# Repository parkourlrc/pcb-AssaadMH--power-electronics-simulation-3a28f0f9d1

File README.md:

# Power Electronics Design & Simulation Suite
> AC power controllers, a 0–10 V industrial dimmer, a digital tachometer and a brushless drive, designed and simulated end to end.
`2025` · `Proteus` · `Power electronics` · `Analog design` · `Microcontroller` · `PSIM`

## About

A body of power-electronics design work carried through schematic capture and full mixed-signal simulation before any board was built.

It covers phase-angle AC power controllers (including a capacitive-trigger variant), a 0–10 V industrial power regulator matching the standard control-signal interface used on drives and dimmable ballasts, a microcontroller-based digital tachometer, and a brushless motor drive — alongside characterisation work on transistor stages and power amplifiers.

Simulating first is the point: switching topologies punish the difference between a circuit that works on paper and one that survives a real inductive load.

## Contents

```
captures/
docs/
kicad/
```

## Notes

## Documents

- [`docs/gradateur-0-10V-projet-tutore.pptx`](docs/gradateur-0-10V-projet-tutore.pptx): the tutored-project defence for the **0-10 V power dimmer** (ENIG, 2024/2025), by Mahmoudi Lassaad, Omri Salim and Dhaoui Chahin. It covers the 7812 supply, the LM358 stage, the PWM power control, the simulation and the PCB. The related boards are `kicad/VARIATEUR_0_10V/` and `kicad/GRADATEUR_DE_PUISSANCE/`.

## Third-party work used here

Everything in this repository is my own work. It builds on the following, which are **not** mine and are used under their own licences:

- **KiCad** by KiCad project — <https://kicad.org>
- **Proteus Design Suite** by Labcenter Electronics — <https://labcenter.com>

## Author

Lassaad Mahmoudi — <assaadmahmoudi0@gmail.com>  
https://linkedin.com/in/mahmoudi-assaad

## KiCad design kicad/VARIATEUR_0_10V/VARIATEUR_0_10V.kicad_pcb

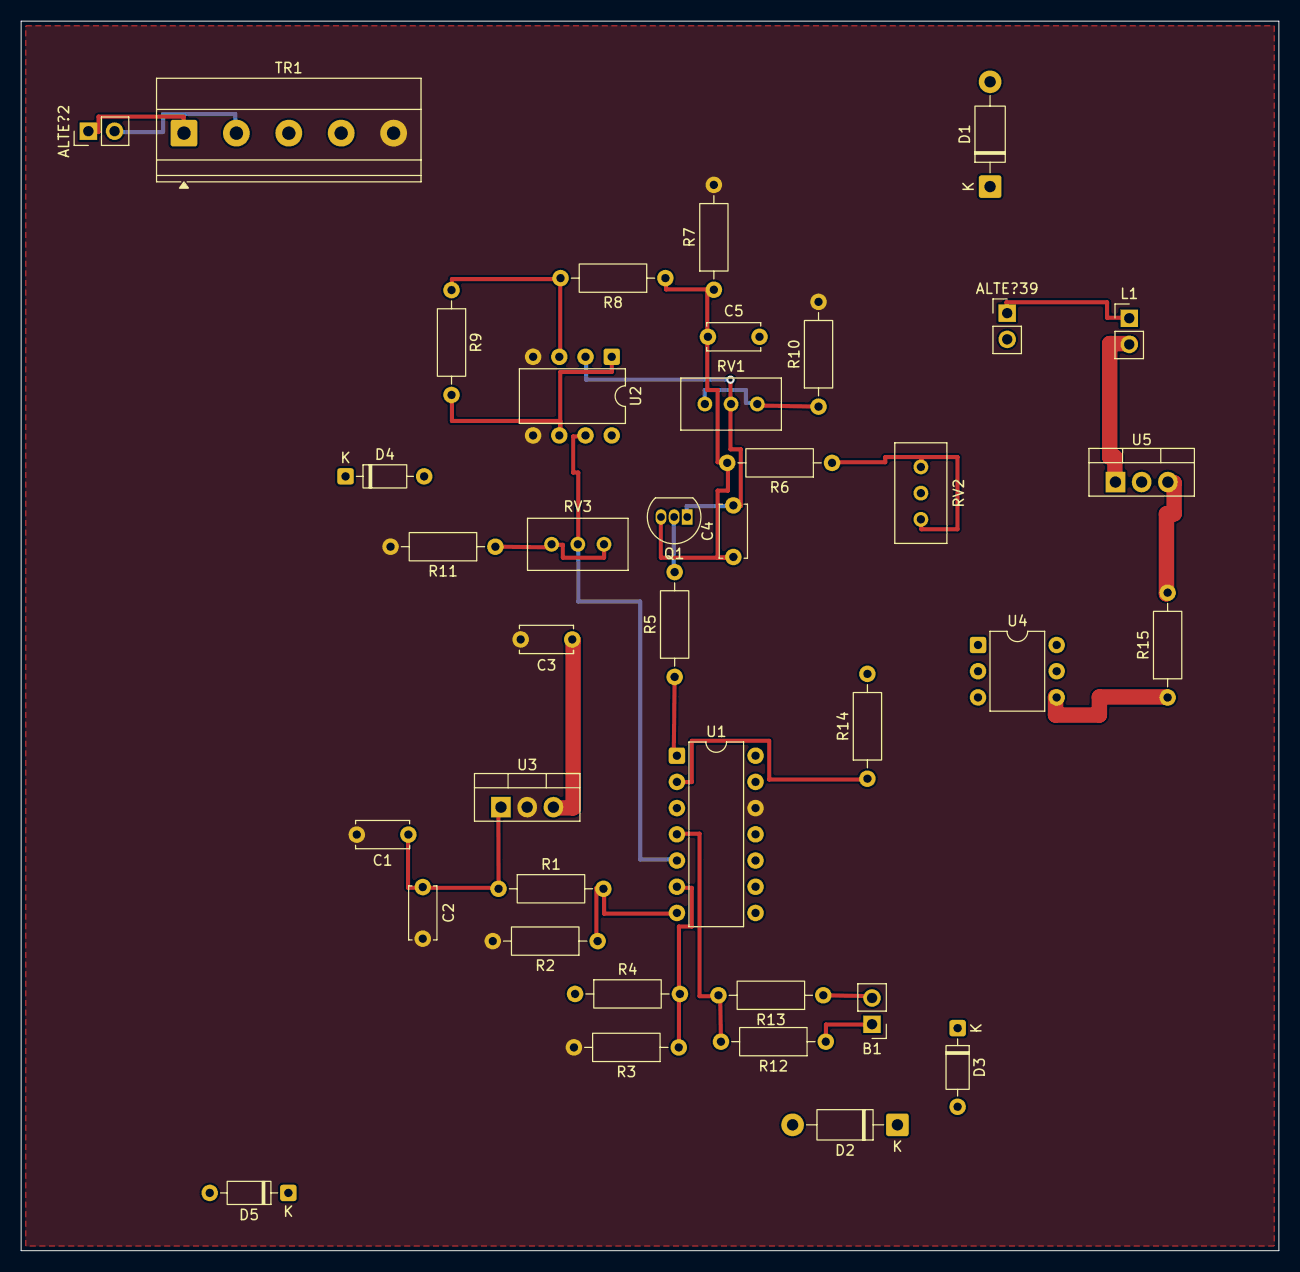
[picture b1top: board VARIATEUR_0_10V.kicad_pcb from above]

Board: 2 copper layers, 121.9 x 119.2 mm, 39 parts (0 on the bottom side), 27 nets.

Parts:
ALTE?2, ALTE?39: ALTERNATOR; PinHeader_1x02_P2.54mm_Vertical
B1: 0V; PinHeader_1x02_P2.54mm_Vertical
C1: 2200uF; C_Disc_D5.0mm_W2.5mm_P5.00mm
C2, C3, C5: 1uF; C_Disc_D5.0mm_W2.5mm_P5.00mm
C4: 100nF; C_Disc_D5.0mm_W2.5mm_P5.00mm
D1, D2: 1N4007; D_DO-41_SOD81_P10.16mm_Horizontal
D3, D4, D5: 1N4148; D_DO-35_SOD27_P7.62mm_Horizontal
L1: 220V; PinHeader_1x02_P2.54mm_Vertical
Q1: BC557; TO-92_Inline
R1, R5, R8, R9, R10, R12, R13: 100k; R_Axial_DIN0207_L6.3mm_D2.5mm_P10.16mm_Horizontal
R2, R3, R6, R7, R11: 10k; R_Axial_DIN0207_L6.3mm_D2.5mm_P10.16mm_Horizontal
R4: 33k; R_Axial_DIN0207_L6.3mm_D2.5mm_P10.16mm_Horizontal
R14, R15: 1k; R_Axial_DIN0207_L6.3mm_D2.5mm_P10.16mm_Horizontal
RV1, RV3: 100k; Potentiometer_Bourns_3296W_Vertical
RV2: 10k; Potentiometer_Bourns_3296W_Vertical
TR1: TRAN-2P3S; TerminalBlock_Phoenix_MKDS-1,5-5-5.08_1x05_P5.08mm_Horizont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
U1: LM339; DIP-14_W7.62mm
U2: LM358; DIP-8_W7.62mm
U3: 7812; TO-220-3_Vertical
U4: MOC3023; DIP-6_W7.62mm
U5: BTB16-600BW; TO-220-3_Vertical

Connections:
GND: C1.2, C2.2, C3.2, R2.2, R3.2, R7.2, R10.2, R11.2, TR1.5, U1.12, U2.4, U2.5, U3.2
N002: C3.1, RV2.2, U1.3, U2.8, U3.3, U4.1
N003: C4.1, C5.1, Q1.3, R6.2, R7.1, R8.1
N004: C1.1, C2.1, R1.1, U3.1
N005: C4.2, Q1.1, RV1.2, U2.2
N006: R3.1, R4.2, U1.6
N007: Q1.2, R5.2
N008: R9.2, U2.1, U2.6
N009: RV3.2, U1.5, U2.7
N013: R1.2, R2.1, U1.7
N014: R6.1, RV2.1, RV2.3
N015: R8.2, R9.1, U2.3
N016: R10.1, RV1.1, RV1.3
N017: R11.1, RV3.1, RV3.3
N018: ALTE?39.2, U4.6, U5.2
N019: R12.2, R13.2, U1.4
N020: ALTE?39.1, L1.1
N021: ALTE?2.1, TR1.1
N022: ALTE?2.2, TR1.2
N023: R5.1, U1.1
N024: R14.2, U4.2
N025: R15.1, U4.4
N026: L1.2, U5.1
N027: R15.2, U5.3
N028: B1.1, R12.1
N029: B1.2, R13.1
N030: R14.1, U1.2

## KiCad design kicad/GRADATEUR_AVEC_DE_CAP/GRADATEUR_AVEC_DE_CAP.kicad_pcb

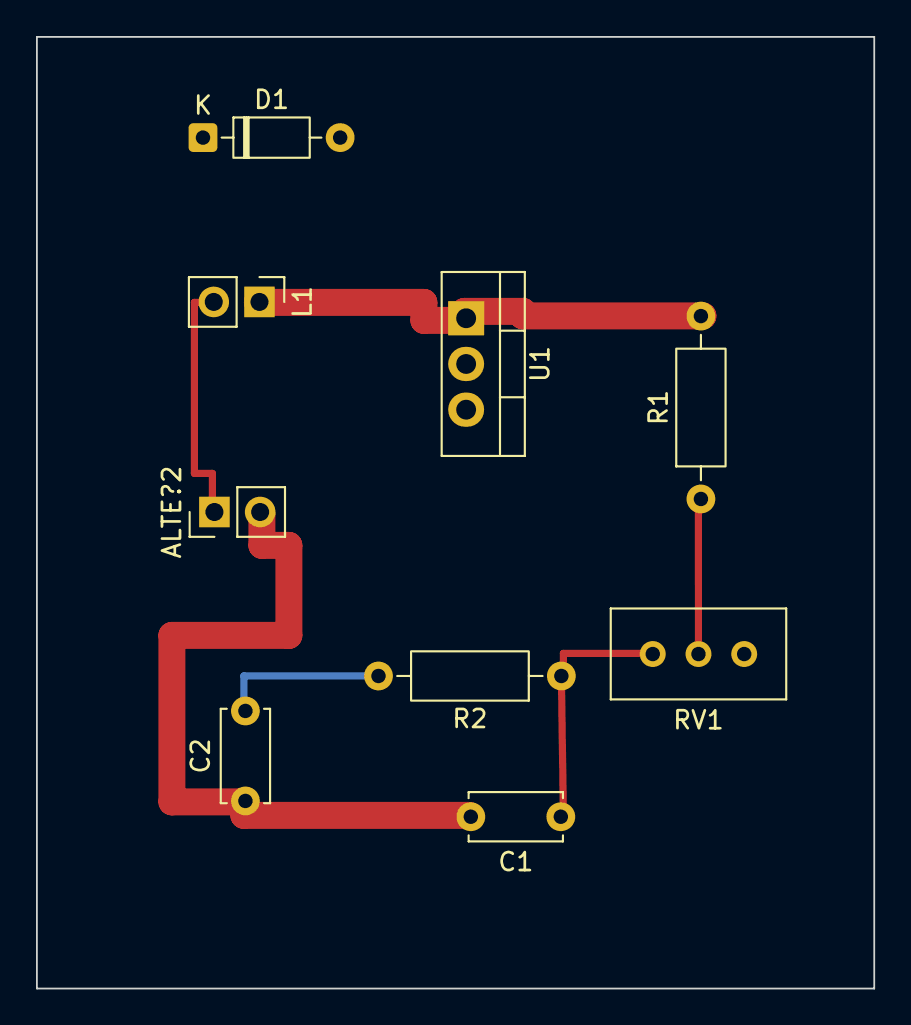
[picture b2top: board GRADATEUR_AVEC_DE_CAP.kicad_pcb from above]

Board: 2 copper layers, 46.5 x 52.9 mm, 9 parts (0 on the bottom side), 6 nets.

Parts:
ALTE?2: ALTERNATOR; PinHeader_1x02_P2.54mm_Vertical
C1: 47nF; C_Disc_D5.0mm_W2.5mm_P5.00mm
C2: 33nF; C_Disc_D5.0mm_W2.5mm_P5.00mm
D1: DB3; D_DO-35_SOD27_P7.62mm_Horizontal
L1: LAMP; PinHeader_1x02_P2.54mm_Vertical
R1: 4.7k; R_Axial_DIN0207_L6.3mm_D2.5mm_P10.16mm_Horizontal
R2: 15k; R_Axial_DIN0207_L6.3mm_D2.5mm_P10.16mm_Horizontal
RV1: POT-HG; Potentiometer_Bourns_3296W_Vertical
U1: TRIAC; TO-220-3_Vertical

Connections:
N001: ALTE?2.2, C1.2, C2.1, U1.2
N002: ALTE?2.1, L1.2
N003: L1.1, R1.2, U1.1
N004: C1.1, R2.1, RV1.1
N005: C2.2, R2.2
N006: R1.1, RV1.2

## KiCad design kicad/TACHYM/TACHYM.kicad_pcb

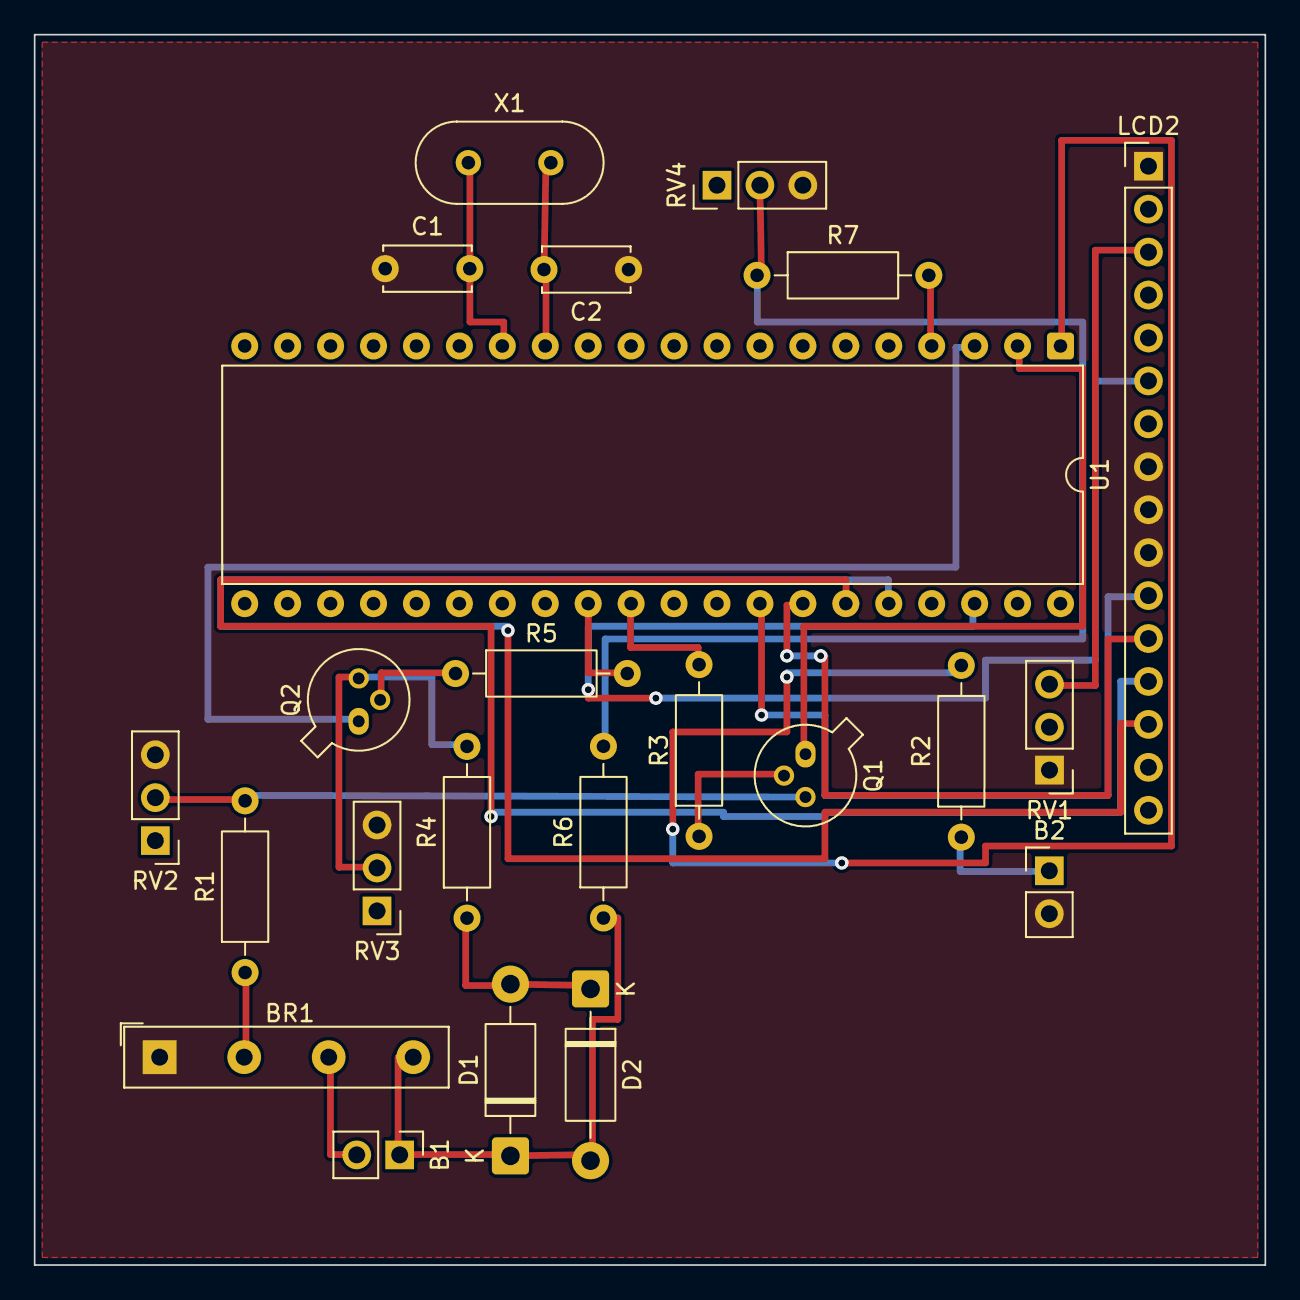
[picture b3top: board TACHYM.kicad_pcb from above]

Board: 2 copper layers, 72.8 x 72.8 mm, 23 parts (0 on the bottom side), 25 nets.

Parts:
B1: 80; PinHeader_1x02_P2.54mm_Vertical
B2: 5V; PinHeader_1x02_P2.54mm_Vertical
BR1: B125C1000; Diode_Bridge_19.0x3.5x10.0mm_P5.0mm
C1, C2: 22pF; C_Disc_D5.0mm_W2.5mm_P5.00mm
D1, D2: 1N4007; D_DO-41_SOD81_P10.16mm_Horizontal
LCD2: LCD 2X16; PinHeader_1x16_P2.54mm_Vertical
Q1, Q2: 2N2222; TO-18-3
R1, R2, R3, R5, R6, R7: 10k; R_Axial_DIN0207_L6.3mm_D2.5mm_P10.16mm_Horizontal
R4: 1k; R_Axial_DIN0207_L6.3mm_D2.5mm_P10.16mm_Horizontal
RV1: 1K; PinHeader_1x03_P2.54mm_Vertical
RV2: 2k; PinHeader_1x03_P2.54mm_Vertical
RV3: 10k; PinHeader_1x03_P2.54mm_Vertical
RV4: 2000; PinHeader_1x03_P2.54mm_Vertical
U1: PIC16F877A; DIP-40_W15.24mm
X1: CRYSTAL; Crystal_HC49-U_Vertical

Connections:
GND: B2.2, BR1.1, C1.1, C2.1, LCD2.1, LCD2.8, LCD2.9, LCD2.10, RV1.1, RV2.3, RV3.3, RV4.3
N002: B1.1, BR1.4, D1.1, D2.2, R6.1
N003: C1.2, U1.14, X1.1
N004: C2.2, U1.13, X1.2
N005: B2.1, R2.1, RV1.2
N006: Q1.3, R1.2, RV2.2
N007: Q2.3, R4.2, RV3.2
N008: D1.2, D2.1, R4.1
N009: R6.2, R7.1, RV4.2
N010: Q1.1, U1.2
N011: Q2.1, U1.3
N012: R7.2, U1.4
N013: LCD2.6, U1.38
N014: LCD2.14, U1.36
N015: LCD2.13, U1.35
N016: LCD2.12, U1.34
N017: LCD2.11, U1.33
N018: R3.2, U1.30
N019: R5.2, U1.29
N020: R2.2, U1.1
N021: LCD2.3, RV1.3
N022: BR1.2, R1.1
N023: B1.2, BR1.3
N024: Q1.2, R3.1
N025: Q2.2, R5.1

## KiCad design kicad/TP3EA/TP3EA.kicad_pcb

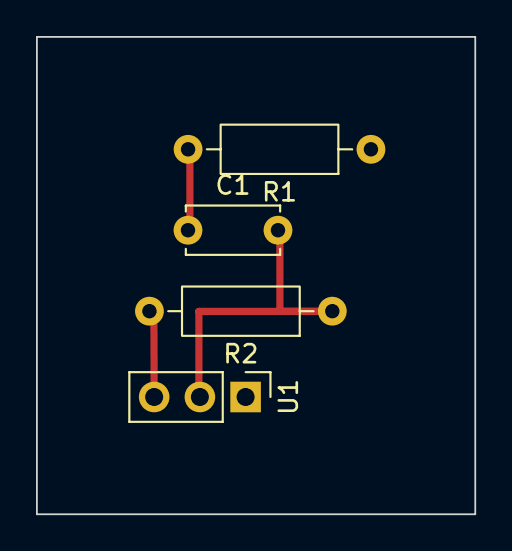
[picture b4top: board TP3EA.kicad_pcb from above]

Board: 2 copper layers, 24.4 x 26.5 mm, 4 parts (0 on the bottom side), 3 nets.

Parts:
C1: 1nF; C_Disc_D5.0mm_W2.5mm_P5.00mm
R1: 10k; R_Axial_DIN0207_L6.3mm_D2.5mm_P10.16mm_Horizontal
R2: 20k; R_Axial_DIN0207_L6.3mm_D2.5mm_P10.16mm_Horizontal
U1: OPAMP; PinHeader_1x03_P2.54mm_Vertical

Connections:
N001: C1.2, R2.1, U1.2
N002: R2.2, U1.3
N003: C1.1, R1.2

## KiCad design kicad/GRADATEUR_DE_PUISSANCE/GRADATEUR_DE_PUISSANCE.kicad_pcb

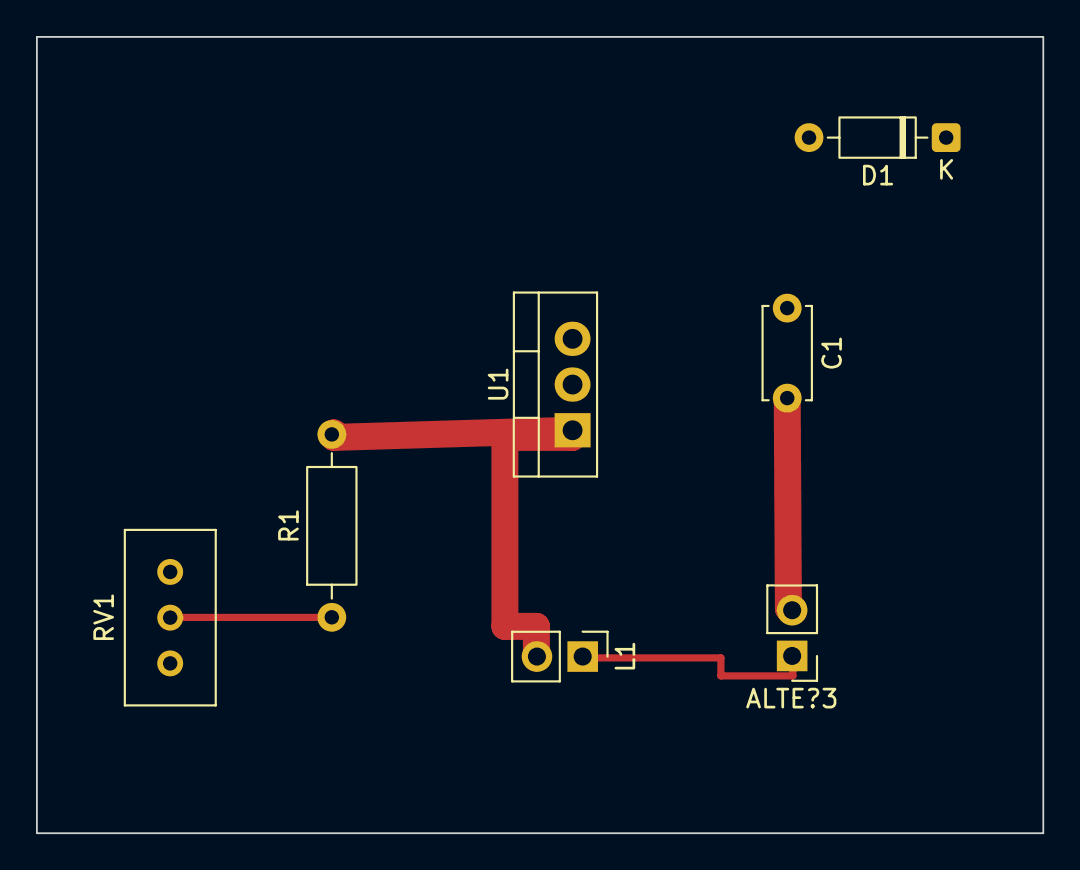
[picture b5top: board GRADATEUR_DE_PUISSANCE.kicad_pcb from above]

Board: 2 copper layers, 55.9 x 44.2 mm, 7 parts (0 on the bottom side), 4 nets.

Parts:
ALTE?3: ALTERNATOR; PinHeader_1x02_P2.54mm_Vertical
C1: 470nF; C_Disc_D5.0mm_W2.5mm_P5.00mm
D1: DB3; D_DO-35_SOD27_P7.62mm_Horizontal
L1: LAMP; PinHeader_1x02_P2.54mm_Vertical
R1: 10k; R_Axial_DIN0207_L6.3mm_D2.5mm_P10.16mm_Horizontal
RV1: POT-HG; Potentiometer_Bourns_3296W_Vertical
U1: TRIAC; TO-220-3_Vertical

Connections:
N001: L1.2, R1.2, U1.1
N002: ALTE?3.2, C1.2, U1.2
N003: ALTE?3.1, L1.1
N006: R1.1, RV1.2
